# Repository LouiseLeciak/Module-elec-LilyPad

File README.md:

# Lily's Pad

## Quick start

### How to flash

> [!warning]
> To flash you need `avr-gcc`, `avr-objcopy`, `avr-dude`

```bash
$> make flash
```

### How to start

Plug and switch the Lily's Pad on, have fun !

## Overview

Lily's Pad is a simple interactive and educational object primarily intended for
children, teachers/educational teams, and families

It allows users to familiarize themselves with the alphabet and numbers in
French Sign Language (FSL) or British Sign Language (BSL), as chosen.

Lily's Pad is also accessible for hearing users who are curious or who have
hearing-impaired loved ones they would like to communicate with.

## Pinout

### ATmega2560 - Power and quartz

| Name  |       Pin(s)        |
| :---: | :-----------------: |
|  GND  | 11, 32, 62, 81, 99  |
|  VCC  | 10, 31, 61, 80, 100 |
| XTAL1 |         34          |
| XTAL2 |         33          |

### ATmega2560 - Resets

|       Name        |   Pin(s)   |
| :---------------: | :--------: |
|   RESET ATmega    | 30 (RESET) |
| RESET Main screen |  7 (PE5)   |
|    RESET Eyes     |  17 (PH5)  |

### ATMega2560 - AVR ISP

| Name  |   Pin(s)   |
| :---: | :--------: |
|  SCK  |  20 (PB1)  |
| MOSI  |  21 (PB2)  |
| MISO  |  22 (PB3)  |
| RESET | 30 (RESET) |

### ATmega2560 - SPI

|         Name         |  Pin(s)  |
| :------------------: | :------: |
|          SS          | 19 (PB0) |
|         SCK          | 20 (PB1) |
|         MOSI         | 21 (PB2) |
|         MISO         | 22 (PB3) |
| Data/Command Screens | 18 (PH6) |
|    SS Main screen    | 6 (PE4)  |
|     SS Left eye      | 16 (PH4) |
|     SS Right eye     | 15 (PH3) |
|        SS SD         | 9 (PE7)  |
|    Backlight/LED     | 8 (PE6)  |

### ATmega2560 - UART

| Name | Pin(s)  |
| :--: | :-----: |
| RX0  | 2 (PE0) |
| TX0  | 3 (PE1) |

### ATmega2560 - Keyboard rows

| Name |  Pin(s)  |
| :--: | :------: |
|  C1  | 57 (PC4) |
|  C2  | 58 (PC5) |
|  C3  | 59 (PC6) |
|  C4  | 60 (PC7) |
|  C5  | 63 (PJ0) |
|  C6  | 64 (PJ1) |
|  C7  | 65 (PJ2) |
|  C8  | 66 (PJ3) |
|  C9  | 67 (PJ4) |
| C10  | 68 (PJ5) |

### ATmega2560 - Keyboard lines

| Name |  Pin(s)  |
| :--: | :------: |
|  R1  | 53 (PC0) |
|  R2  | 54 (PC1) |
|  R3  | 55 (PC2) |
|  R4  | 56 (PC3) |

### ATmega2560 - Rotary encoder and slide switch

|      Name      |  Pin(s)  |
| :------------: | :------: |
|      SDA       | 44 (PD1) |
|      SCL       | 43 (PD0) |
| Slide switch 1 | 69 (PJ6) |
| Slide switch 2 | 70 (PG2) |
| Slide switch 3 | 71 (PA7) |

## Update firmware

Download update.sh in the latest releases section and run it.
The script can take one argument for the theme.

```bash
# cd inside the directory where update.sh is located
$> chmod +x update.sh
$> ./update.sh <DEVICE PORT> <OPTIONAL: THEME>
```

## Features

An LCD screen connected to a keyboard featuring letters and numbers.
A rotary encoder allowing users to scroll through FSL/ASL signs on the screen.
A clickable rotary encoder to confirm an input.
A USB Type-C port to power the device.
A power button to turn the device on/off.
A 3D-printed casing around the screen.
A 3D-printed base in which the keyboard is embedded.
A slide switch to change language, English (ASL) or French (FSL).
Two small LCD screens to display animated eyes.
Translation/game/alphabet modes.

## Generate Doxygen static website

> [!warning]
> To use this, you need doxygen installed on your system.

Run the following command:

```
make doc
```

## Small presentation video

[Video](https://youtu.be/IG8Irz5PA7s?is=ZnnKCJjxfxXaESvo)

## Documentation

|         DOC          |                               Lien                               |
| :------------------: | :--------------------------------------------------------------: |
|    Specifications    | [CDC Lily's Pad](https://docs.google.com/document/d/1O8xM8pXDJNO5zp6k8G5bc-3bWXDQlbUf1931MdxXfck/edit?tab=t.0#heading=h.v1wg8mrqdu4q)                |
|      Prototype       | [Prototypage](https://docs.google.com/document/d/1rZbFsAjX72JkaI_FbCfIp4b-ht4Qgn11_CjMCb2TPow/edit?tab=t.0)                      |
| Problemes&Solutions  | [Problèmes & Solutions](https://docs.google.com/document/d/1paDHATY-Msma2sKo5jREeCfTP951xgNia56kSwROvPU/edit?tab=t.0#heading=h.edi7yypwj845)  |
|      User guide      | [User guide](https://docs.google.com/document/d/11DVUBJalhqJB5Wq1R7DtcMrKvT6OBZJyWIw1Wtvbu1M/edit?tab=t.0#heading=h.yum7i86vcbuq)       |

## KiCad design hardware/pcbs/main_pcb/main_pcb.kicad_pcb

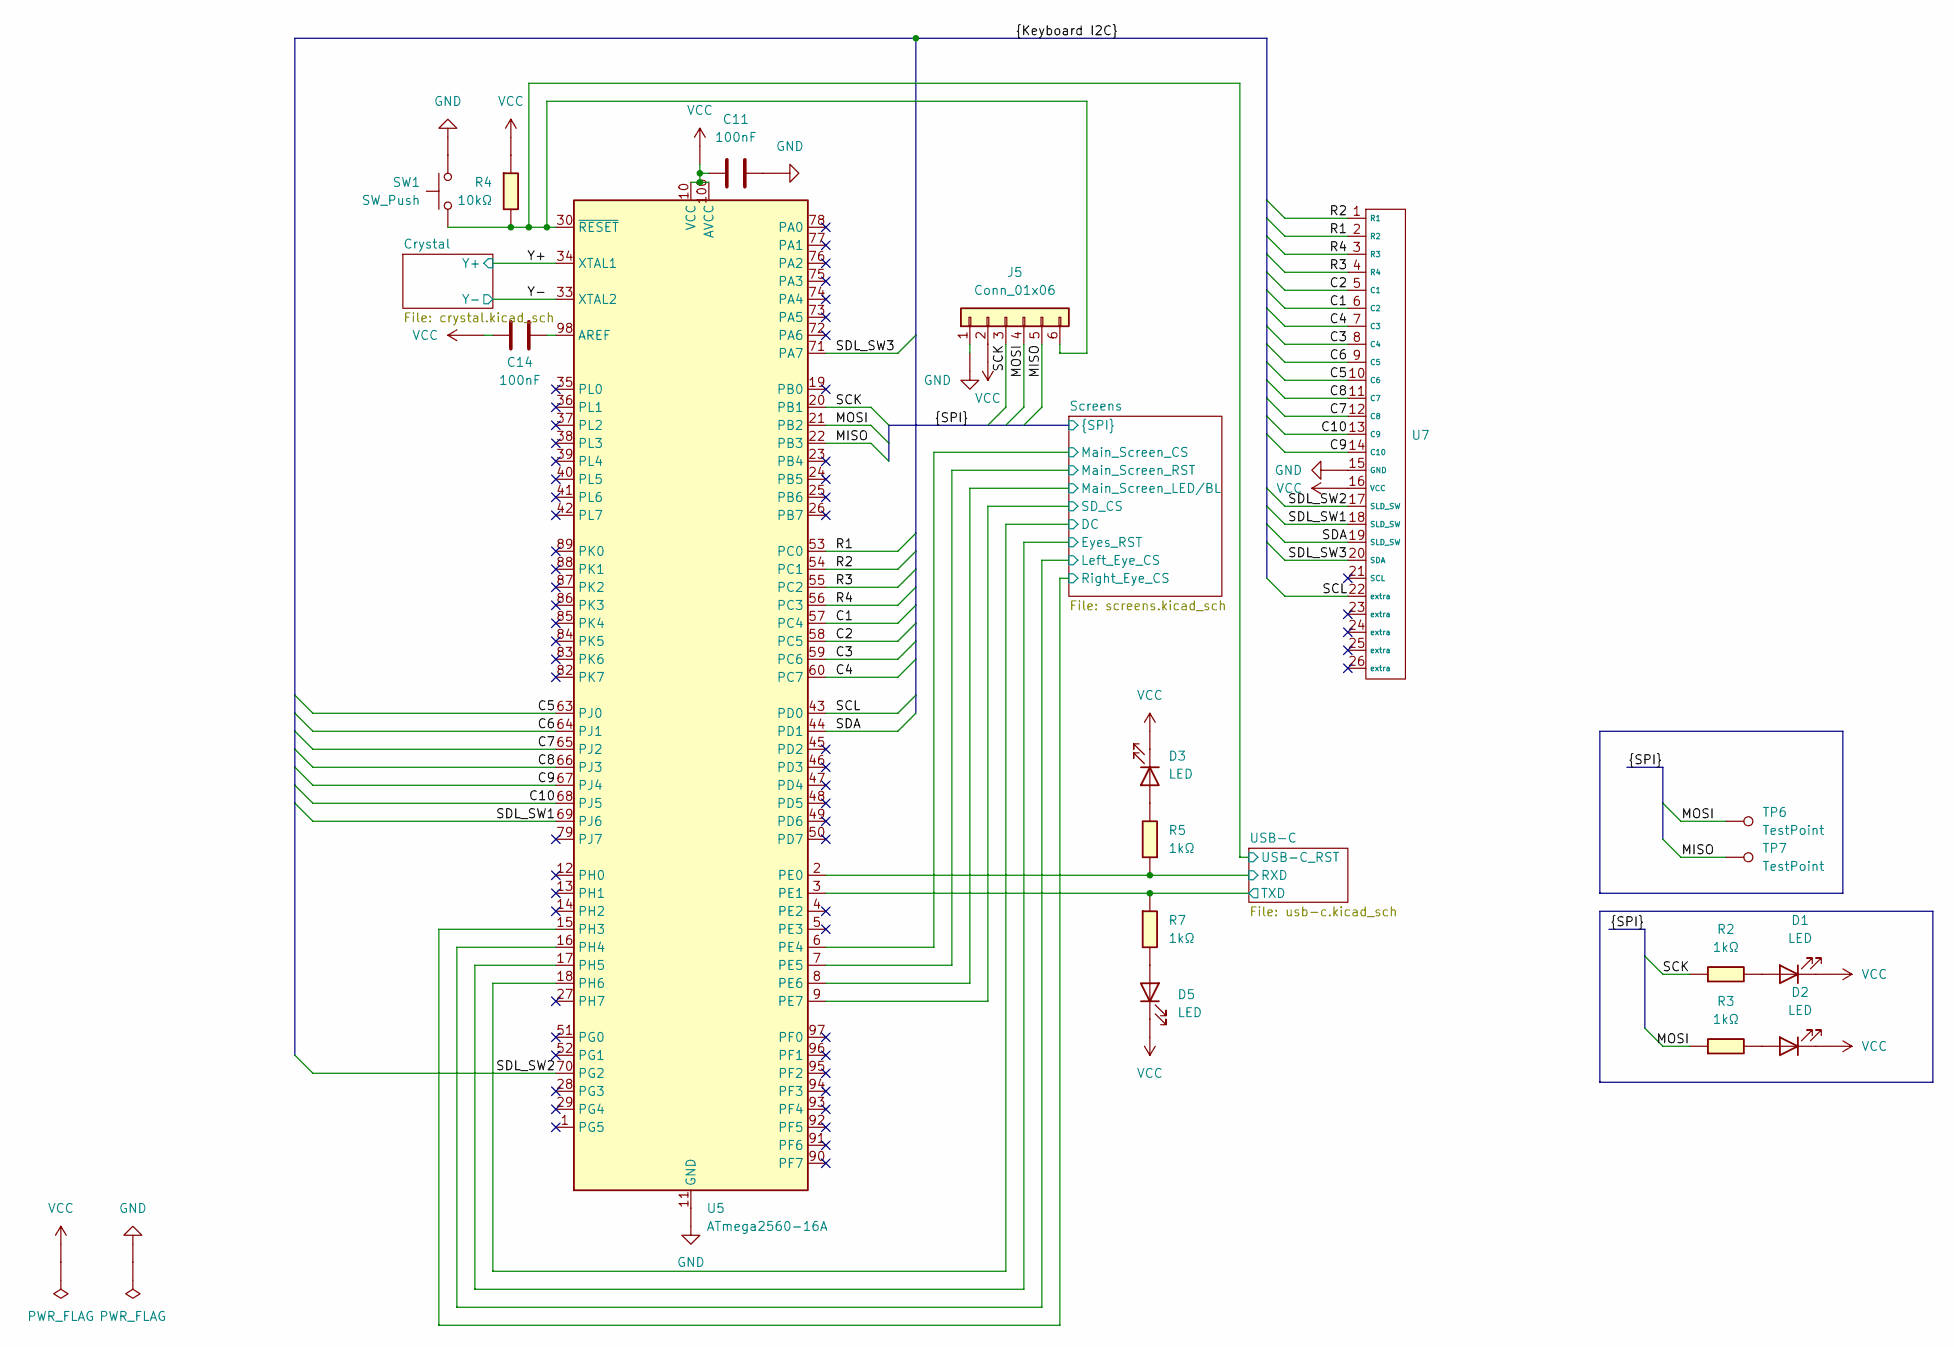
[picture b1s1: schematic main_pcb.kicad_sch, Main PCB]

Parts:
C11, C14: 100nF; Capacitor_0603; LCSC C14663
D1, D2, D3, D5: LED; LED_0603; LCSC C19171394
J5: Conn_01x06; Pin_1x06_2.54mm_Vertical
R2, R3, R5, R7: 1kΩ; Resistor_0603; LCSC C22548
R4: 10kΩ; Resistor_0603; LCSC C98220
SW1: SW_Push; Switch_Push_Button_12mm; LCSC C84931
TP6, TP7: TestPoint; Test point
U5: ATmega2560-16A; ATmega2560-16AU; LCSC C22460
U7: AMPHENOL_69830-026LF; LCSC C397108

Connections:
/C1: U5.57 (PC4), U7.6 (C2)
/C2: U5.58 (PC5), U7.5 (C1)
/C3: U5.59 (PC6), U7.8 (C4)
/C4: U5.60 (PC7), U7.7 (C3)
/C5: U5.63 (PJ0), U7.10 (C6)
/C6: U5.64 (PJ1), U7.9 (C5)
/C7: U5.65 (PJ2), U7.12 (C8)
/C8: U5.66 (PJ3), U7.11 (C7)
/C9: U5.67 (PJ4), U7.14 (C10)
/C10: U5.68 (PJ5), U7.13 (C9)
/MISO: J5.5, TP7.1, U5.22 (PB3); also elsewhere on the board
/MOSI: J5.4, R3.1, TP6.1, U5.21 (PB2); also elsewhere on the board
/R1: U5.53 (PC0), U7.2 (R2)
/R2: U5.54 (PC1), U7.1 (R1)
/R3: U5.55 (PC2), U7.4 (R4)
/R4: U5.56 (PC3), U7.3 (R3)
/SCK: J5.3, R2.1, U5.20 (PB1); also elsewhere on the board
/SCL: U5.43 (PD0), U7.22 (extra)
/SDA: U5.44 (PD1), U7.19 (SLD_SW)
/SDL_SW1: U5.69 (PJ6), U7.18 (SLD_SW)
/SDL_SW2: U5.70 (PG2), U7.17 (SLD_SW)
/SDL_SW3: U5.71 (PA7), U7.20 (SDA)
/Screens/DC: U5.18 (PH6); also elsewhere on the board
/Screens/Eyes_RST: U5.17 (PH5); also elsewhere on the board
/Screens/Left_Eye_CS: U5.16 (PH4); also elsewhere on the board
/Screens/Main_Screen_CS: U5.6 (PE4); also elsewhere on the board
/Screens/Main_Screen_LED/BL: U5.8 (PE6); also elsewhere on the board
/Screens/Main_Screen_RST: U5.7 (PE5); also elsewhere on the board
/Screens/Right_Eye_CS: U5.15 (PH3); also elsewhere on the board
/Screens/SD_CS: U5.9 (PE7); also elsewhere on the board
/USB-C/RXD: R5.1, U5.2 (PE0); also elsewhere on the board
/USB-C/TXD: R7.1, U5.3 (PE1); also elsewhere on the board
/USB-C/USB-C_RST: J5.6, R4.2, SW1.1, U5.30 (~RESET); also elsewhere on the board
/Y+: U5.34 (XTAL1); also elsewhere on the board
/Y-: U5.33 (XTAL2); also elsewhere on the board
GND: C11.2, J5.1, SW1.2, U5.11 (GND), U5.32 (GND), U5.62 (GND), U5.81 (GND), U5.99 (GND), U7.15 (GND); also elsewhere on the board
unnamed: D1.2 (A), R2.2
unnamed: D2.2 (A), R3.2
unnamed: D3.2 (A), R5.2
unnamed: D5.2 (A), R7.2
unnamed: C14.2, U5.98 (AREF)
VCC: C11.1, C14.1, D1.1 (K), D2.1 (K), D3.1 (K), D5.1 (K), J5.2, R4.1, U5.10 (VCC), U5.31 (VCC), U5.61 (VCC), U5.80 (VCC), U5.100 (AVCC), U7.16 (VCC); also elsewhere on the board

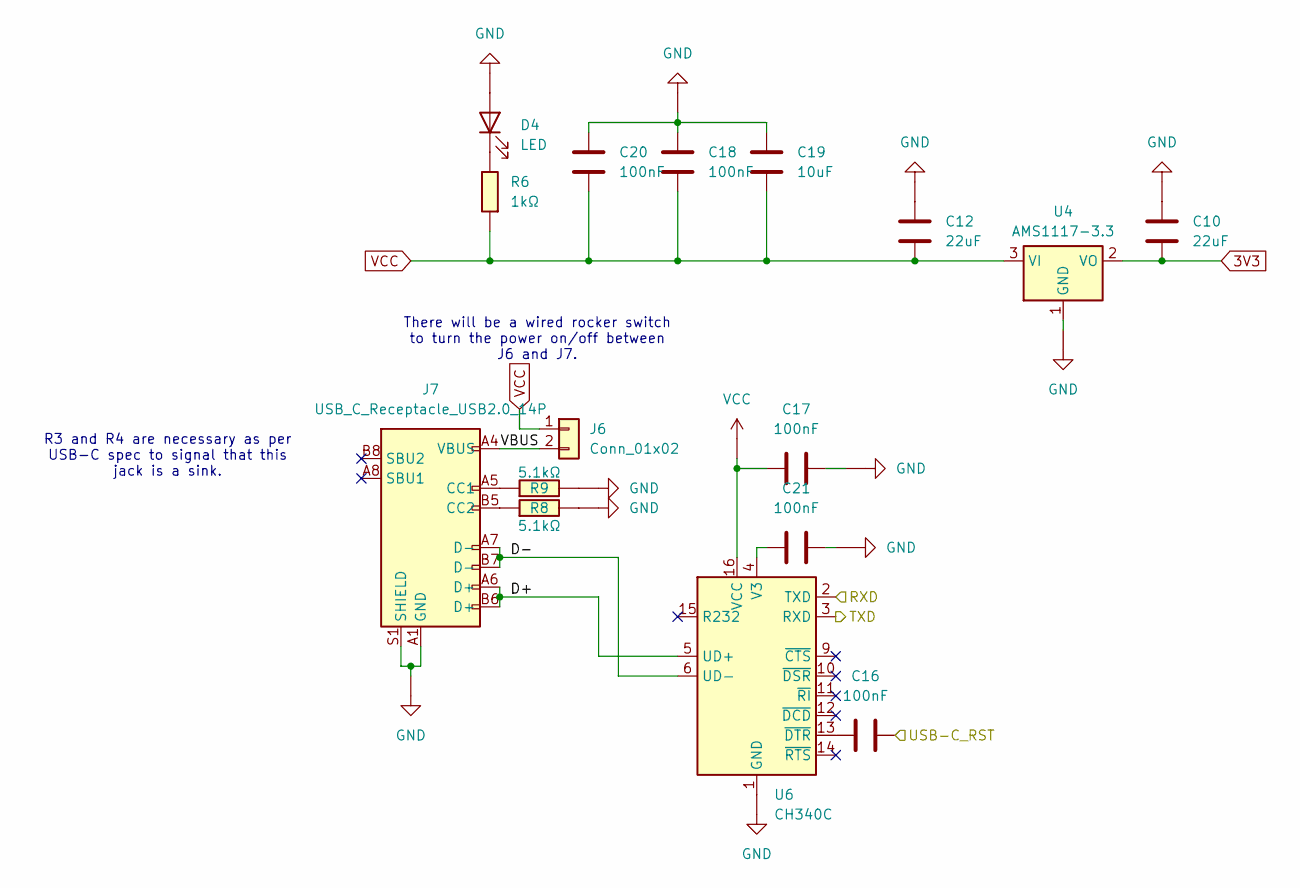
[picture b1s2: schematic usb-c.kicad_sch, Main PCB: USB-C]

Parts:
C10, C12: 22uF; Capacitor_0603; LCSC C2762594
C16, C17, C18, C20, C21: 100nF; Capacitor_0603; LCSC C14663
C19: 10uF; Capacitor_0603; LCSC C1691
D4: LED; LED_0603; LCSC C19171394
J6: Conn_01x02; JST XH 2 pins
J7: USB_C_Receptacle_USB2.0_14P; USB_C_Receptacle_HRO_TYPE-C-31-M-12; LCSC C165948
R6: 1kΩ; Resistor_0603; LCSC C22548
R8, R9: 5.1kΩ; Resistor_0603; LCSC C2907044
U4: AMS1117-3.3; SOT-223-3_TabPin2_AMS1117; LCSC C5205141
U6: CH340C; SOP-16_CH340C; LCSC C84681

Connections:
3V3: C10.2, U4.2 (VO); also elsewhere on the board
/USB-C/D+: J7.A6 (D+), J7.B6 (D+), U6.5 (UD+)
/USB-C/D-: J7.A7 (D-), J7.B7 (D-), U6.6 (UD-)
/USB-C/RXD: U6.2 (TXD); also elsewhere on the board
/USB-C/TXD: U6.3 (RXD); also elsewhere on the board
/USB-C/USB-C_RST: C16.2; also elsewhere on the board
/USB-C/VBUS: J6.2, J7.A4 (VBUS), J7.A9 (VBUS), J7.B4 (VBUS), J7.B9 (VBUS)
GND: C10.1, C12.1, C17.2, C18.1, C19.1, C20.1, C21.2, D4.2 (A), J7.A1 (GND), J7.A12 (GND), J7.B1 (GND), J7.B12 (GND), J7.S1 (SHIELD), R8.2, R9.2, U4.1 (GND), U6.1 (GND); also elsewhere on the board
unnamed: D4.1 (K), R6.2
unnamed: J7.A5 (CC1), R9.1
unnamed: J7.B5 (CC2), R8.1
unnamed: C21.1, U6.4 (V3)
unnamed: C16.1, U6.13 (~DTR)
VCC: C12.2, C17.1, C18.2, C19.2, C20.2, J6.1, R6.1, U4.3 (VI), U6.16 (VCC); also elsewhere on the board

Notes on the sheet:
R3 and R4 are necessary as per USB-C spec to signal that this jack is a sink.
There will be a wired rocker switch to turn the power on/off between J6 and J7.

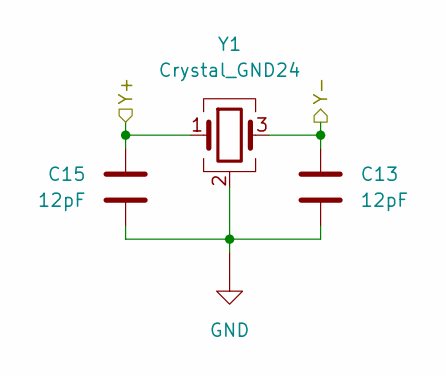
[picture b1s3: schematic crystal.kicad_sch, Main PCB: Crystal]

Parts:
C13, C15: 12pF; Capacitor_0603; LCSC C107034
Y1: Crystal_GND24; Crystal_3225; LCSC C13738

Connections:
/Y+: C15.2, Y1.1; also elsewhere on the board
/Y-: C13.2, Y1.3; also elsewhere on the board
GND: C13.1, C15.1, Y1.2 (GND), Y1.4 (G); also elsewhere on the board

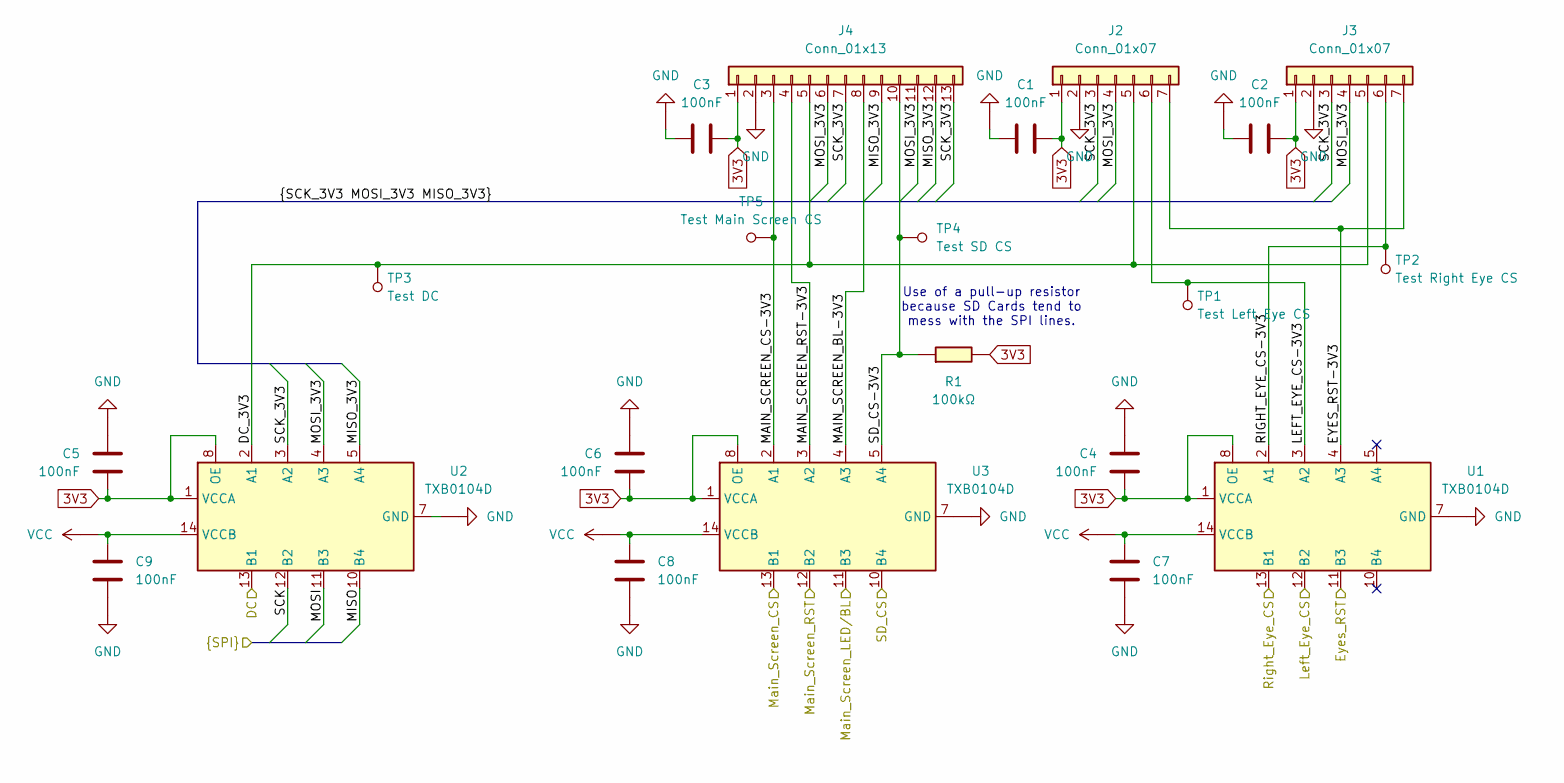
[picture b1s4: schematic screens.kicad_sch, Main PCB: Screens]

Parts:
C1, C2, C3, C4, C5, C6, C7, C8, C9: 100nF; Capacitor_0603; LCSC C14663
J2, J3: Conn_01x07; Pin_1x07_2.54mm_Vertical
J4: Conn_01x13; Pin_1x13_2.54mm_Vertical
R1: 100kΩ; Resistor_0603; LCSC C2906980
TP1: Test Left Eye CS; Test point
TP2: Test Right Eye CS; Test point
TP3: Test DC; Test point
TP4: Test SD CS; Test point
TP5: Test Main Screen CS; Test point
U1, U2, U3: TXB0104D; SOIC-14_TXB0104DR; LCSC C2652946

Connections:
3V3: C1.2, C2.2, C3.2, C4.2, C5.2, C6.2, J2.1, J3.1, J4.1, R1.2, U1.1 (VCCA), U1.8 (OE), U2.1 (VCCA), U2.8 (OE), U3.1 (VCCA), U3.8 (OE); also elsewhere on the board
/MISO: U2.10 (B4); also elsewhere on the board
/MOSI: U2.11 (B3); also elsewhere on the board
/SCK: U2.12 (B2); also elsewhere on the board
/Screens/DC: U2.13 (B1); also elsewhere on the board
/Screens/DC_3V3: J2.5, J3.5, J4.5, TP3.1, U2.2 (A1)
/Screens/EYES_RST-3V3: J2.7, J3.7, U1.4 (A3)
/Screens/Eyes_RST: U1.11 (B3); also elsewhere on the board
/Screens/LEFT_EYE_CS-3V3: J2.6, TP1.1, U1.3 (A2)
/Screens/Left_Eye_CS: U1.12 (B2); also elsewhere on the board
/Screens/MAIN_SCREEN_BL-3V3: J4.8, U3.4 (A3)
/Screens/MAIN_SCREEN_CS-3V3: J4.3, TP5.1, U3.2 (A1)
/Screens/MAIN_SCREEN_RST-3V3: J4.4, U3.3 (A2)
/Screens/MISO_3V3: J4.9, J4.12, U2.5 (A4)
/Screens/MOSI_3V3: J2.4, J3.4, J4.6, J4.11, U2.4 (A3)
/Screens/Main_Screen_CS: U3.13 (B1); also elsewhere on the board
/Screens/Main_Screen_LED/BL: U3.11 (B3); also elsewhere on the board
/Screens/Main_Screen_RST: U3.12 (B2); also elsewhere on the board
/Screens/RIGHT_EYE_CS-3V3: J3.6, TP2.1, U1.2 (A1)
/Screens/Right_Eye_CS: U1.13 (B1); also elsewhere on the board
/Screens/SCK_3V3: J2.3, J3.3, J4.7, J4.13, U2.3 (A2)
/Screens/SD_CS: U3.10 (B4); also elsewhere on the board
/Screens/SD_CS-3V3: J4.10, R1.1, TP4.1, U3.5 (A4)
GND: C1.1, C2.1, C3.1, C4.1, C5.1, C6.1, C7.1, C8.1, C9.1, J2.2, J3.2, J4.2, U1.7 (GND), U2.7 (GND), U3.7 (GND); also elsewhere on the board
VCC: C7.2, C8.2, C9.2, U1.14 (VCCB), U2.14 (VCCB), U3.14 (VCCB); also elsewhere on the board

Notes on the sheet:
Use of a pull-up resistor because SD Cards tend to mess with the SPI lines.

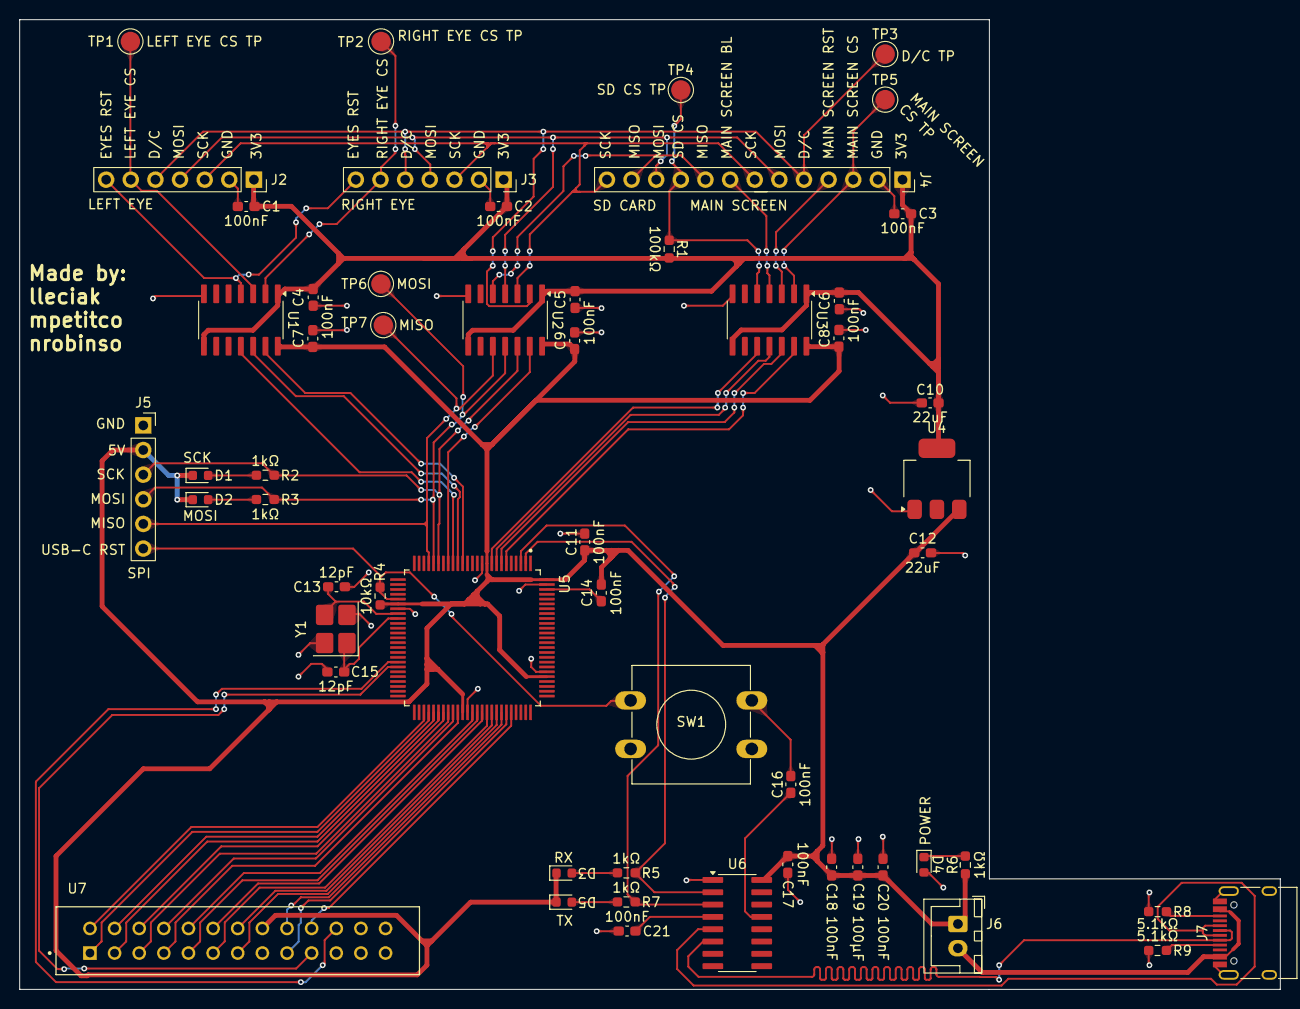
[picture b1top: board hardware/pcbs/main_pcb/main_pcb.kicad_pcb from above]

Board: 2 copper layers, 130.0 x 100.0 mm, 57 parts (0 on the bottom side), 62 nets.

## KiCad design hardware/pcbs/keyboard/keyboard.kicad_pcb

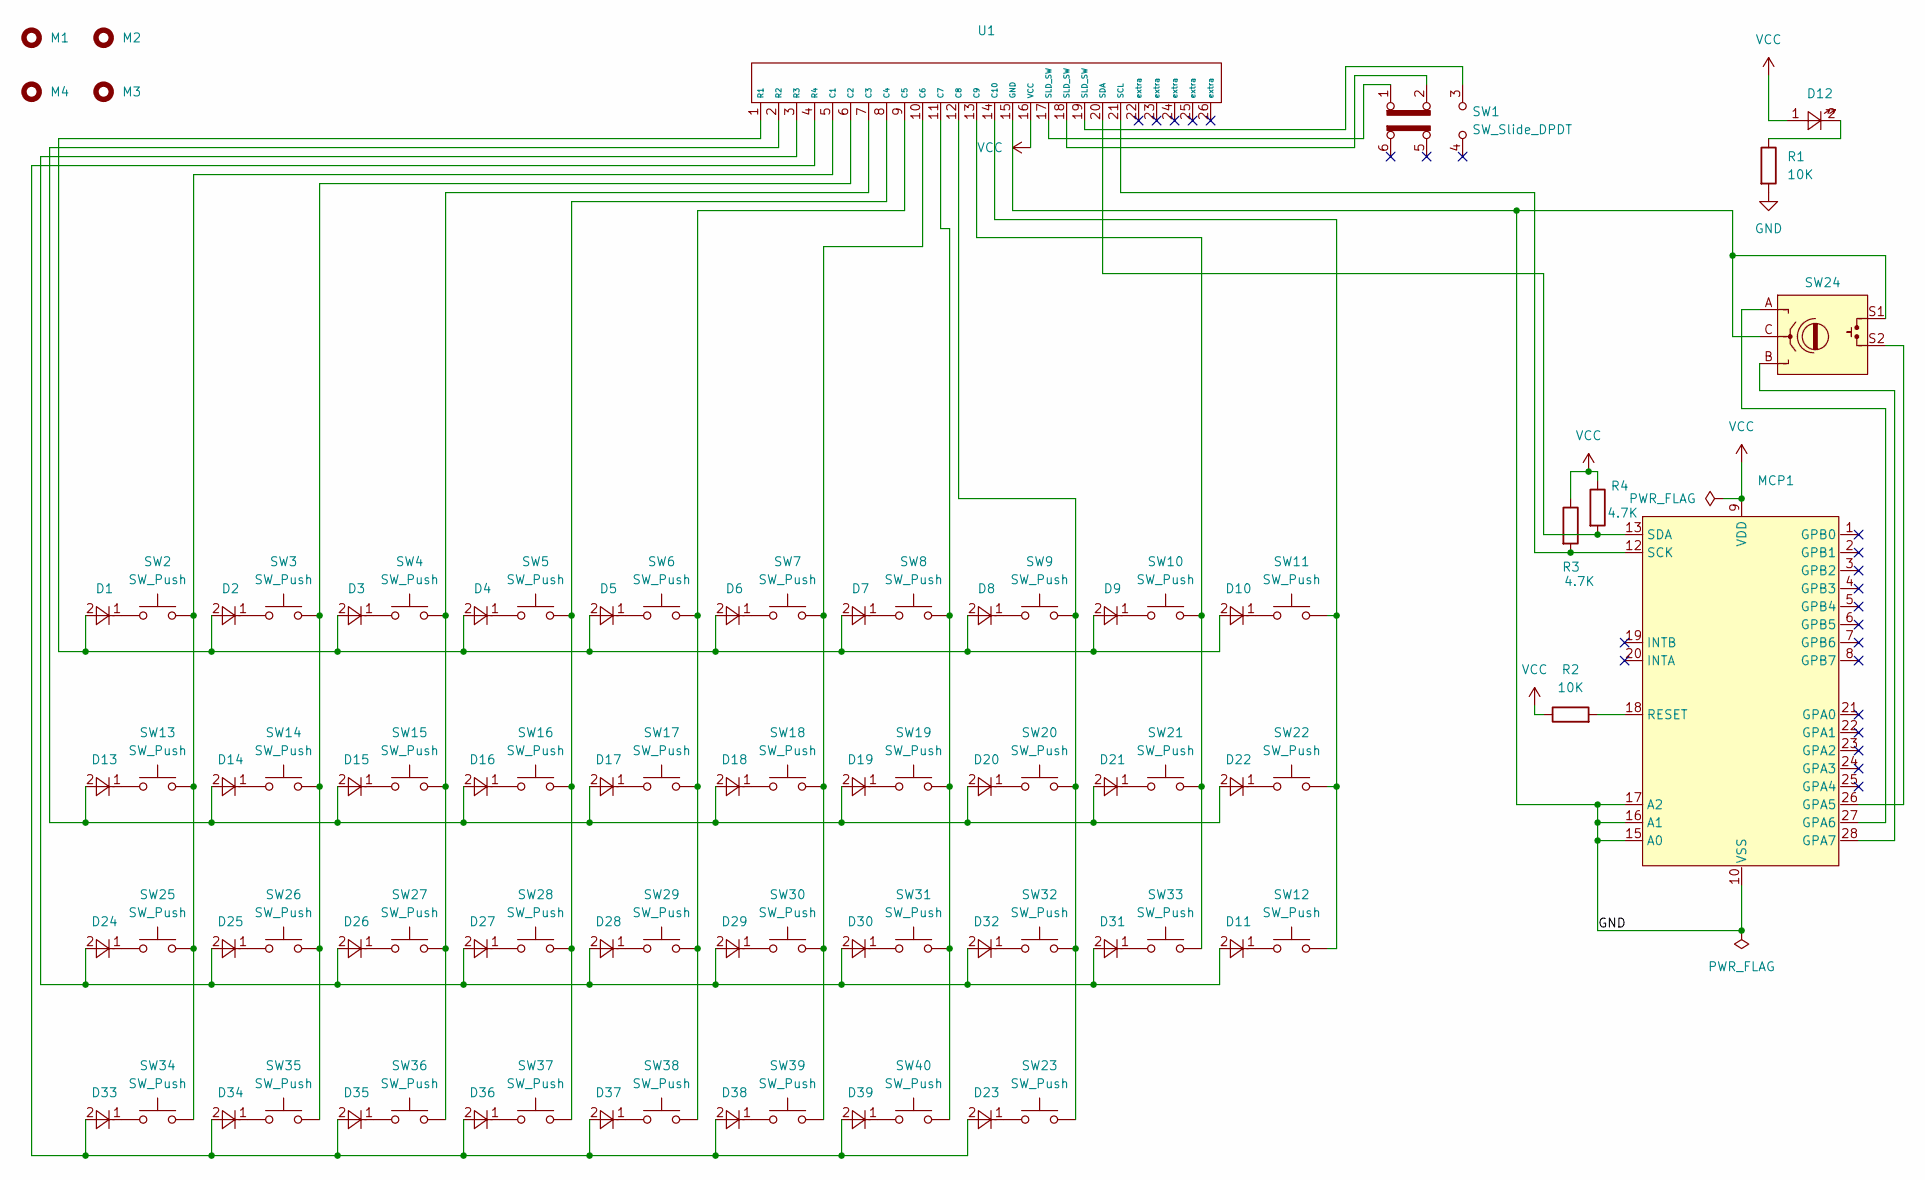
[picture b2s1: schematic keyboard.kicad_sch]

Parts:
D1, D2, D3, D4, D5, D6, D7, D8, D9, D10, D11, D13, D14, D15, D16, D17, D18, D19, D20, D21, D22, D23, D24, D25, D26, D27, D28, D29, D30, D31, D32, D33, D34, D35, D36, D37, D38, D39: diode
D12: led
M1, M2, M3, M4: hole
MCP1: MCP23017
R1, R2: 10K; Resistance
R3, R4: 4.7K; Resistance
SW1: SW_Slide_DPDT; slide_switch
SW2, SW3, SW4, SW5, SW6, SW7, SW8, SW9, SW10, SW11, SW12, SW13, SW14, SW15, SW16, SW17, SW18, SW19, SW20, SW21, SW22, SW23, SW25, SW26, SW27, SW28, SW29, SW30, SW31, SW32, SW33, SW34, SW35, SW36, SW37, SW38, SW39, SW40: SW_Push; push_switch
SW24: rotary_encoder
U1: male_header

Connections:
GND: MCP1.10 (VSS), MCP1.15 (A0), MCP1.16 (A1), MCP1.17 (A2), R1.2, SW24.C, SW24.S1, U1.15 (GND)
unnamed: D1.1, SW2.1
unnamed: D2.1, SW3.1
unnamed: D3.1, SW4.1
unnamed: D4.1, SW5.1
unnamed: D5.1, SW6.1
unnamed: D6.1, SW7.1
unnamed: D7.1, SW8.1
unnamed: D8.1, SW9.1
unnamed: D9.1, SW10.1
unnamed: D10.1, SW11.1
unnamed: D11.1, SW12.1
unnamed: D12.2, R1.1
unnamed: D13.1, SW13.1
unnamed: D14.1, SW14.1
unnamed: D15.1, SW15.1
unnamed: D16.1, SW16.1
unnamed: D17.1, SW17.1
unnamed: D18.1, SW18.1
unnamed: D19.1, SW19.1
unnamed: D20.1, SW20.1
unnamed: D21.1, SW21.1
unnamed: D22.1, SW22.1
unnamed: D23.1, SW23.1
unnamed: D24.1, SW25.1
unnamed: D25.1, SW26.1
unnamed: D26.1, SW27.1
unnamed: D27.1, SW28.1
unnamed: D28.1, SW29.1
unnamed: D29.1, SW30.1
unnamed: D30.1, SW31.1
unnamed: D31.1, SW33.1
unnamed: D32.1, SW32.1
unnamed: D33.1, SW34.1
unnamed: D34.1, SW35.1
unnamed: D35.1, SW36.1
unnamed: D36.1, SW37.1
unnamed: D37.1, SW38.1
unnamed: D38.1, SW39.1
unnamed: D39.1, SW40.1
unnamed: MCP1.26 (GPA5), SW24.S2
unnamed: MCP1.27 (GPA6), SW24.A
unnamed: MCP1.28 (GPA7), SW24.B
unnamed: MCP1.18 (RESET), R2.2
unnamed: MCP1.12 (SCK), R3.2, U1.21 (SCL)
unnamed: MCP1.13 (SDA), R4.2, U1.20 (SDA)
unnamed: SW1.1 (A), U1.17 (SLD_SW)
unnamed: SW1.2 (B), U1.18 (SLD_SW)
unnamed: SW1.3 (C), U1.19 (SLD_SW)
unnamed: SW2.2, SW13.2, SW25.2, SW34.2, U1.5 (C1)
unnamed: SW3.2, SW14.2, SW26.2, SW35.2, U1.6 (C2)
unnamed: SW4.2, SW15.2, SW27.2, SW36.2, U1.7 (C3)
unnamed: SW5.2, SW16.2, SW28.2, SW37.2, U1.8 (C4)
unnamed: SW6.2, SW17.2, SW29.2, SW38.2, U1.9 (C5)
unnamed: SW7.2, SW18.2, SW30.2, SW39.2, U1.10 (C6)
unnamed: SW8.2, SW19.2, SW31.2, SW40.2, U1.11 (C7)
unnamed: SW9.2, SW20.2, SW23.2, SW32.2, U1.12 (C8)
unnamed: SW10.2, SW21.2, SW33.2, U1.13 (C9)
unnamed: SW11.2, SW12.2, SW22.2, U1.14 (C10)
unnamed: D1.2, D2.2, D3.2, D4.2, D5.2, D6.2, D7.2, D8.2, D9.2, D10.2, U1.1 (R1)
unnamed: D13.2, D14.2, D15.2, D16.2, D17.2, D18.2, D19.2, D20.2, D21.2, D22.2, U1.2 (R2)
unnamed: D11.2, D24.2, D25.2, D26.2, D27.2, D28.2, D29.2, D30.2, D31.2, D32.2, U1.3 (R3)
unnamed: D23.2, D33.2, D34.2, D35.2, D36.2, D37.2, D38.2, D39.2, U1.4 (R4)
VCC: D12.1, MCP1.9 (VDD), R2.1, R3.1, R4.1, U1.16 (VCC)

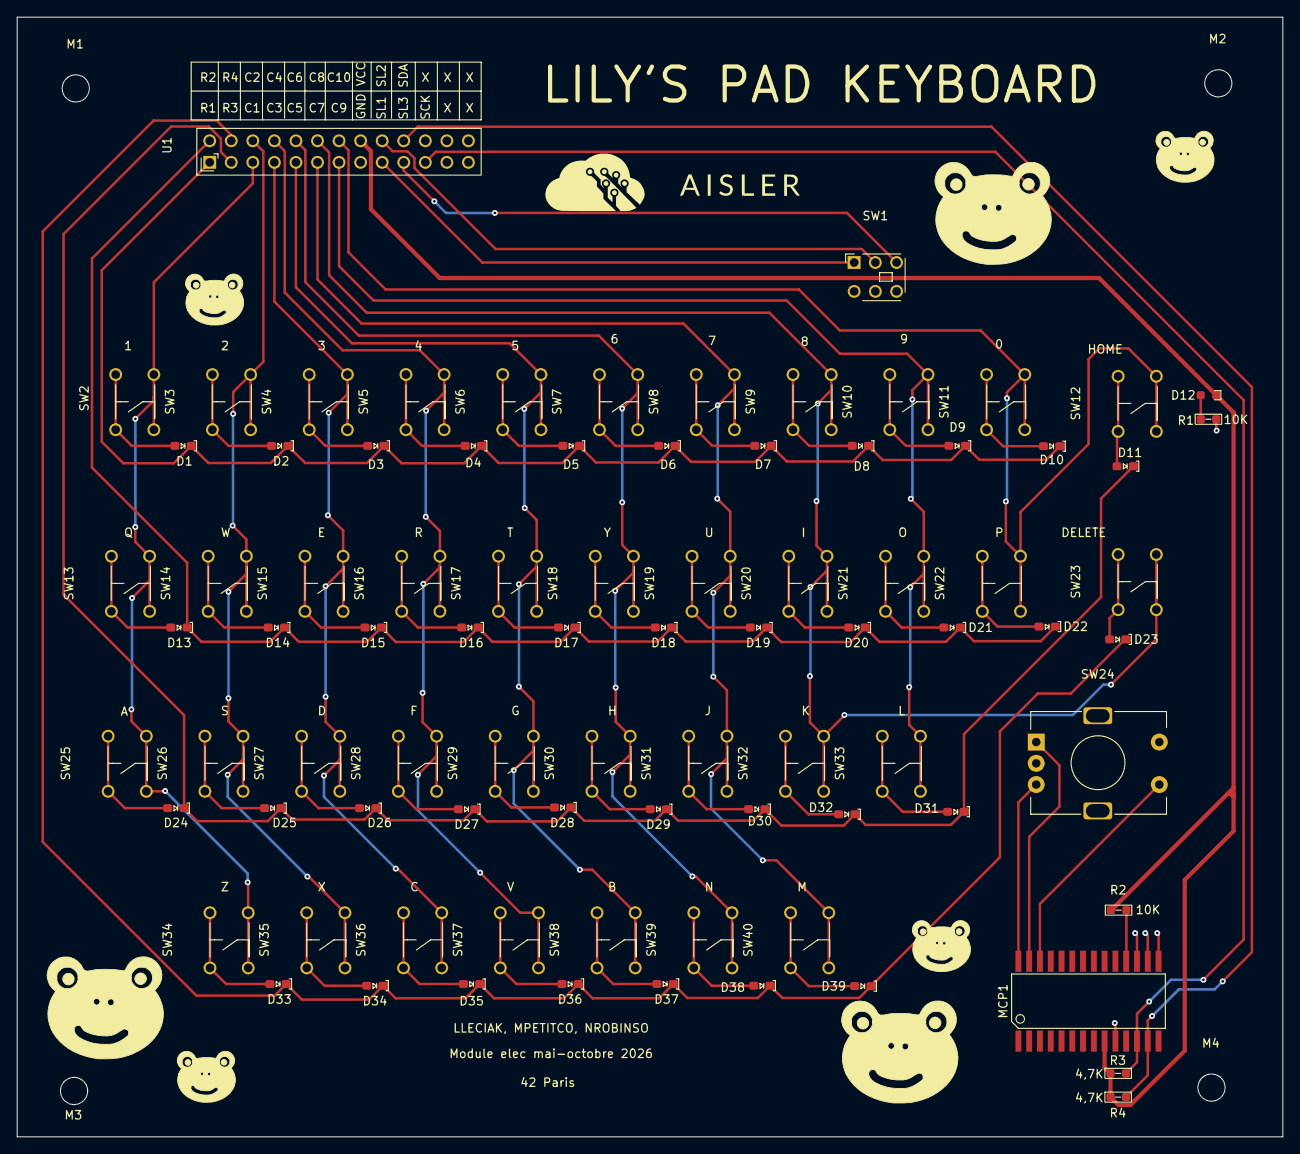
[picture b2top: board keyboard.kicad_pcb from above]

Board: 2 copper layers, 149.1 x 131.9 mm, 89 parts (0 on the bottom side), 64 nets.

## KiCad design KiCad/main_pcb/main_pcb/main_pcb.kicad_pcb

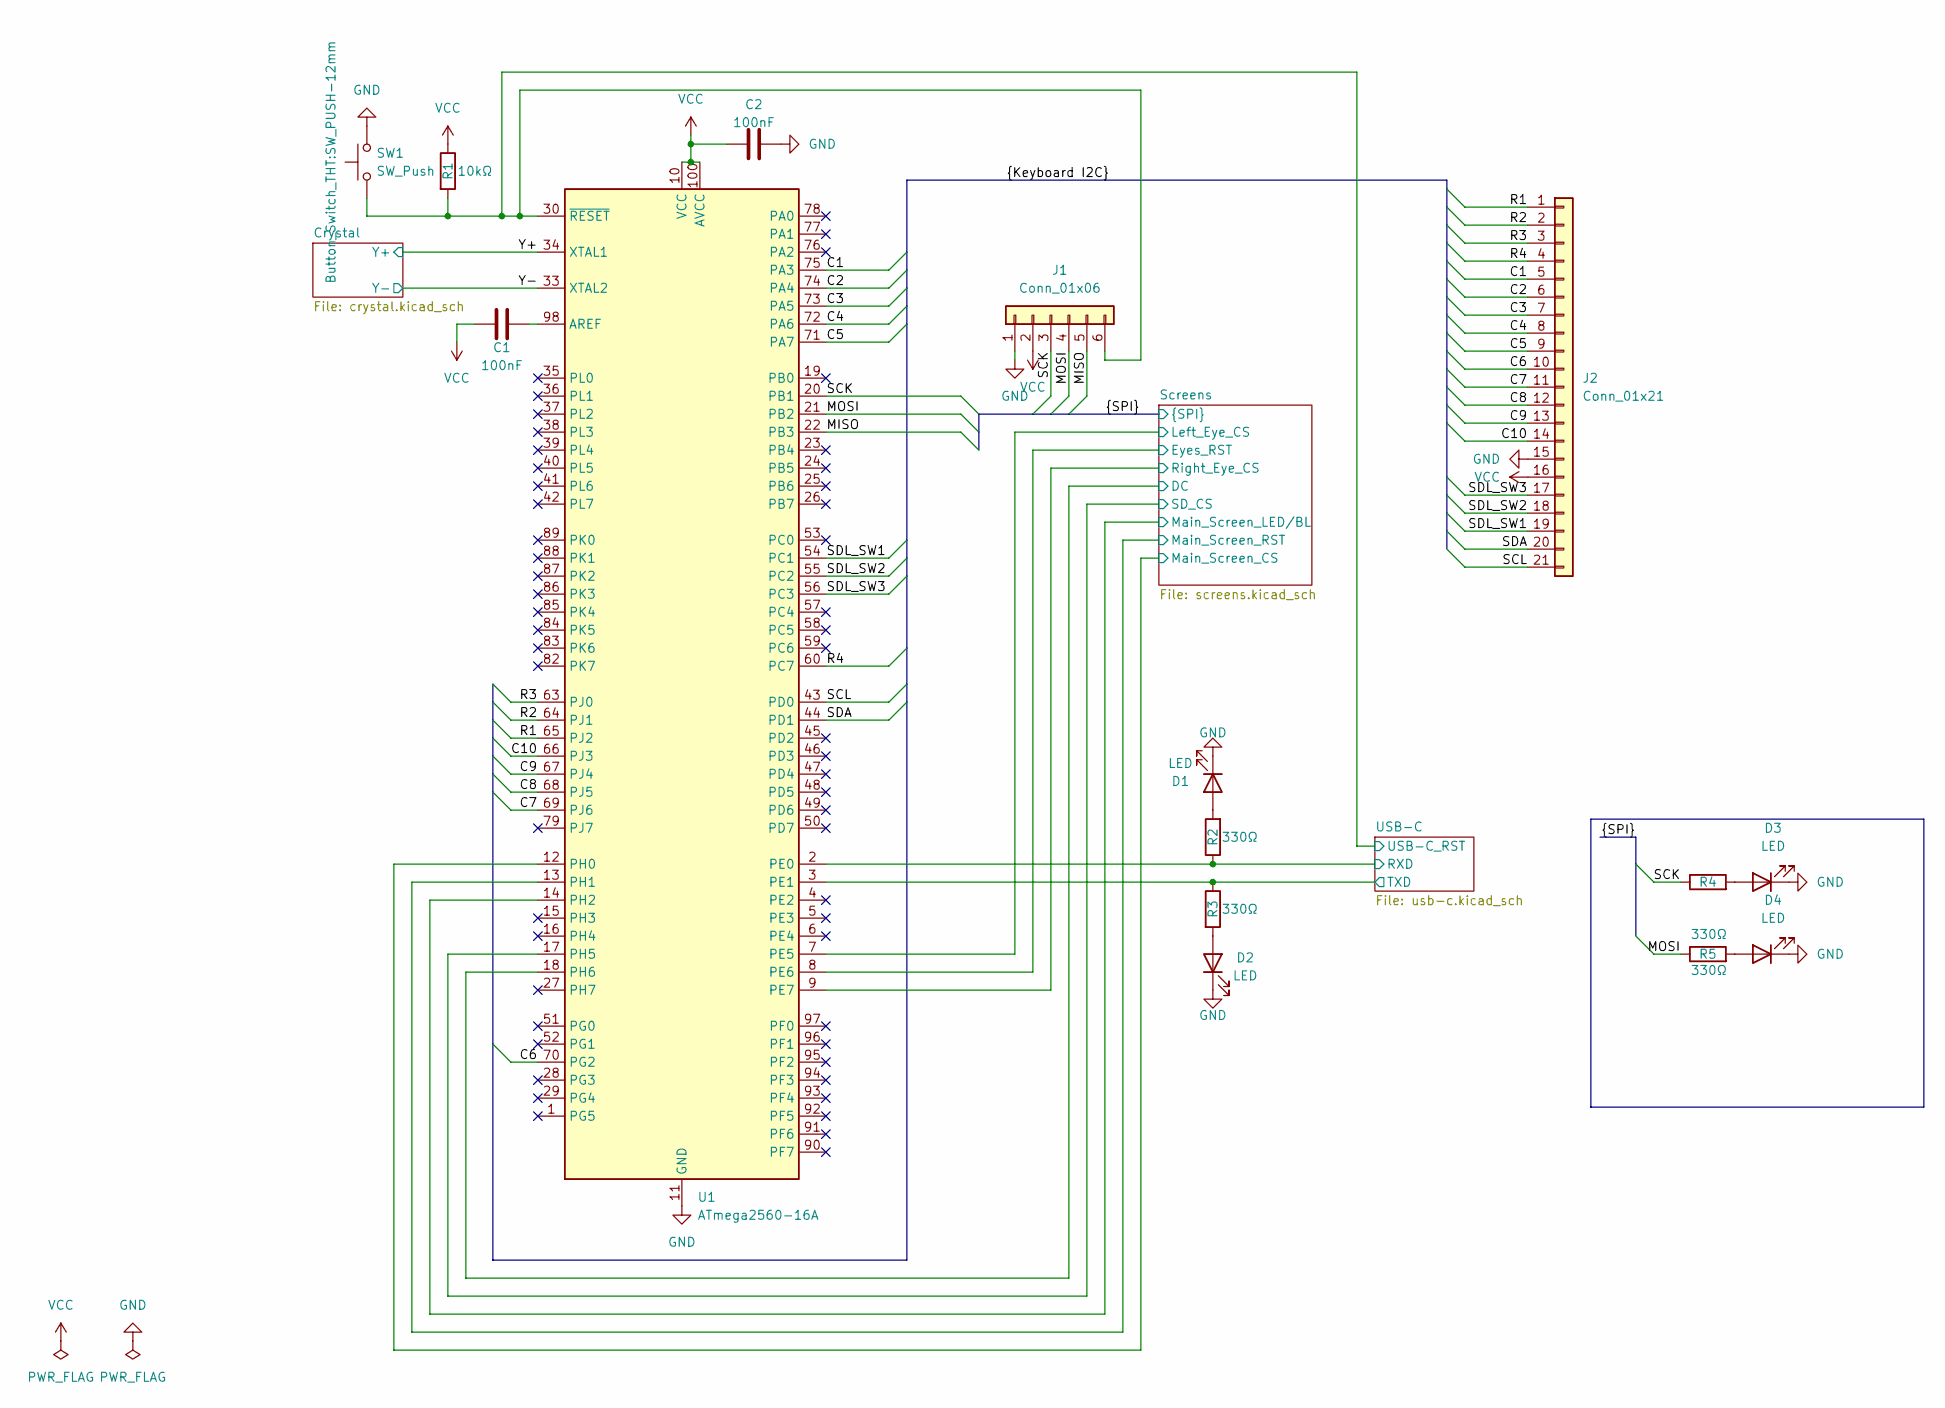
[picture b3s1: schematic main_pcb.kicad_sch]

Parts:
C1, C2: 100nF; C_0603_1608Metric_Pad1.08x0.95mm_HandSolder
D1, D2, D3, D4: LED; LED_0603_1608Metric_Pad1.05x0.95mm_HandSolder
J1: Conn_01x06; PinHeader_1x06_P2.54mm_Vertical
J2: Conn_01x21; PinHeader_1x21_P2.54mm_Vertical
R1: 10kΩ; R_0603_1608Metric_Pad0.98x0.95mm_HandSolder
R2, R3, R4, R5: 330Ω; R_0603_1608Metric_Pad0.98x0.95mm_HandSolder
SW1: SW_Push; SW_PUSH-12mm
U1: ATmega2560-16A; TQFP-100_14x14mm_P0.5mm

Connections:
/C1: J2.5, U1.75 (PA3)
/C2: J2.6, U1.74 (PA4)
/C3: J2.7, U1.73 (PA5)
/C4: J2.8, U1.72 (PA6)
/C5: J2.9, U1.71 (PA7)
/C6: J2.10, U1.70 (PG2)
/C7: J2.11, U1.69 (PJ6)
/C8: J2.12, U1.68 (PJ5)
/C9: J2.13, U1.67 (PJ4)
/C10: J2.14, U1.66 (PJ3)
/MISO: J1.5, U1.22 (PB3); also elsewhere on the board
/MOSI: J1.4, R5.1, U1.21 (PB2); also elsewhere on the board
/R1: J2.1, U1.65 (PJ2)
/R2: J2.2, U1.64 (PJ1)
/R3: J2.3, U1.63 (PJ0)
/R4: J2.4, U1.60 (PC7)
/SCK: J1.3, R4.1, U1.20 (PB1); also elsewhere on the board
/SCL: J2.21, U1.43 (PD0)
/SDA: J2.20, U1.44 (PD1)
/SDL_SW1: J2.19, U1.54 (PC1)
/SDL_SW2: J2.18, U1.55 (PC2)
/SDL_SW3: J2.17, U1.56 (PC3)
/Screens/DC: U1.18 (PH6); also elsewhere on the board
/Screens/Eyes_RST: U1.8 (PE6); also elsewhere on the board
/Screens/Left_Eye_CS: U1.7 (PE5); also elsewhere on the board
/Screens/Main_Screen_CS: U1.12 (PH0); also elsewhere on the board
/Screens/Main_Screen_LED/BL: U1.14 (PH2); also elsewhere on the board
/Screens/Main_Screen_RST: U1.13 (PH1); also elsewhere on the board
/Screens/Right_Eye_CS: U1.9 (PE7); also elsewhere on the board
/Screens/SD_CS: U1.17 (PH5); also elsewhere on the board
/USB-C/RXD: R2.1, U1.2 (PE0); also elsewhere on the board
/USB-C/TXD: R3.1, U1.3 (PE1); also elsewhere on the board
/USB-C/USB-C_RST: J1.6, R1.2, SW1.1, U1.30 (~RESET); also elsewhere on the board
/Y+: U1.34 (XTAL1); also elsewhere on the board
/Y-: U1.33 (XTAL2); also elsewhere on the board
GND: C2.2, D1.1 (K), D2.1 (K), D3.1 (K), D4.1 (K), J1.1, J2.15, SW1.2, U1.11 (GND), U1.32 (GND), U1.62 (GND), U1.81 (GND), U1.99 (GND); also elsewhere on the board
unnamed: D1.2 (A), R2.2
unnamed: D2.2 (A), R3.2
unnamed: D3.2 (A), R4.2
unnamed: D4.2 (A), R5.2
unnamed: C1.2, U1.98 (AREF)
VCC: C1.1, C2.1, J1.2, J2.16, R1.1, U1.10 (VCC), U1.31 (VCC), U1.61 (VCC), U1.80 (VCC), U1.100 (AVCC); also elsewhere on the board
